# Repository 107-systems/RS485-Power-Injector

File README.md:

`RS485-Power-Injector`
======================

This repository contains the design files for [L3X-Z](https://github.com/107-systems/l3xz)'s RS485 power injector which allows to directly inject battery power into the RS485 bus connecting the robot's Dynamixel MX-28AR servos.

<p align="center">
  
</p>

## Debug circuitry

This board contains a circuit with a RS485 driver to drive a LED to show bus activity. This circuit can also be used to interface the RS485 bus to a controller or computer. The circuit can be used with 3.3V and 5V levels. Some parts need to be changed to achieve this.

| **Designator** | **3.3V version** | **5V version** |
|:--------------:|:----------------:|:--------------:|
| U1             | L78L33ACUTR      | L78L05ACUTR    |
| U2             | SP3485EN-L       | SN75176AD      |

## Connectors

### Power Input J1
Anderson Power Pole

| **Pin** | **Signal**    |       **Description**        |
|:-------:|:-------------:|:----------------------------:|
| 1       | +BATT         | Directly to Dynamixel        |
| 2       | GND           |                              |

The input voltage is directly feed to the Dynamixel servo. So the maximum voltage depends solely on the servo used.

### Power Input J2
Würth WR-TBL 3.5mm 2-pin screw terminal.

| **Pin** | **Signal**    |       **Description**        |
|:-------:|:-------------:|:----------------------------:|
| 1       | +BATT         | Directly to Dynamixel        |
| 2       | GND           |                              |

### RS485 Input J3
Würth WR-TBL 3.5mm 3-pin screw terminal.

| **Pin** | **Signal**    |       **Description**        |
|:-------:|:-------------:|:----------------------------:|
| 1       | RS485-A       | Directly to Dynamixel        |
| 2       | RS485-B       | Directly to Dynamixel        |
| 3       | GND           |                              |

### RS485 Input J4
JST GH 1.25mm 4-pin.

| **Pin** | **Signal**    |       **Description**        |
|:-------:|:-------------:|:----------------------------:|
| 1       | +BATT         | to Dynamixel via R2          |
| 2       | RS485-A       | Directly to Dynamixel        |
| 3       | RS485-B       | Directly to Dynamixel        |
| 4       | GND           |                              |

### Dynamixel connectors J5 and J6
In the Dynamixel world there exist two type of connectors: [Molex Mini-SPOX](https://www.molex.com/molex/products/part-detail/pcb_headers/0022035045) and [JST EH](https://www.jst-mfg.com/product/pdf/eng/eEH.pdf).

Both are 2.5 mm pitch and use the same pin out and both can be mounted on the board. So you can decide which one to use and which fits your application and servo.

| **Pin** | **Signal**    |       **Description**        |
|:-------:|:-------------:|:----------------------------:|
| 1       | GND           |                              |
| 2       | +BATT         |                              |
| 3       | RS485-A       |                              |
| 4       | RS485-B       |                              |

### RS485 Debug output J7
Pin header 2.54mm 4-pin.

| **Pin** | **Signal**    |       **Description**        |
|:-------:|:-------------:|:----------------------------:|
| 1       | RS485_TXEN    |                              |
| 2       | RS485_TX      |                              |
| 3       | RS485_RX      |                              |
| 4       | GND           |                              |

## Enclosure

There exists a 3D printable enclosure to encapsulate the PCB.

### Standard

## PCB
### Top

### Bottom

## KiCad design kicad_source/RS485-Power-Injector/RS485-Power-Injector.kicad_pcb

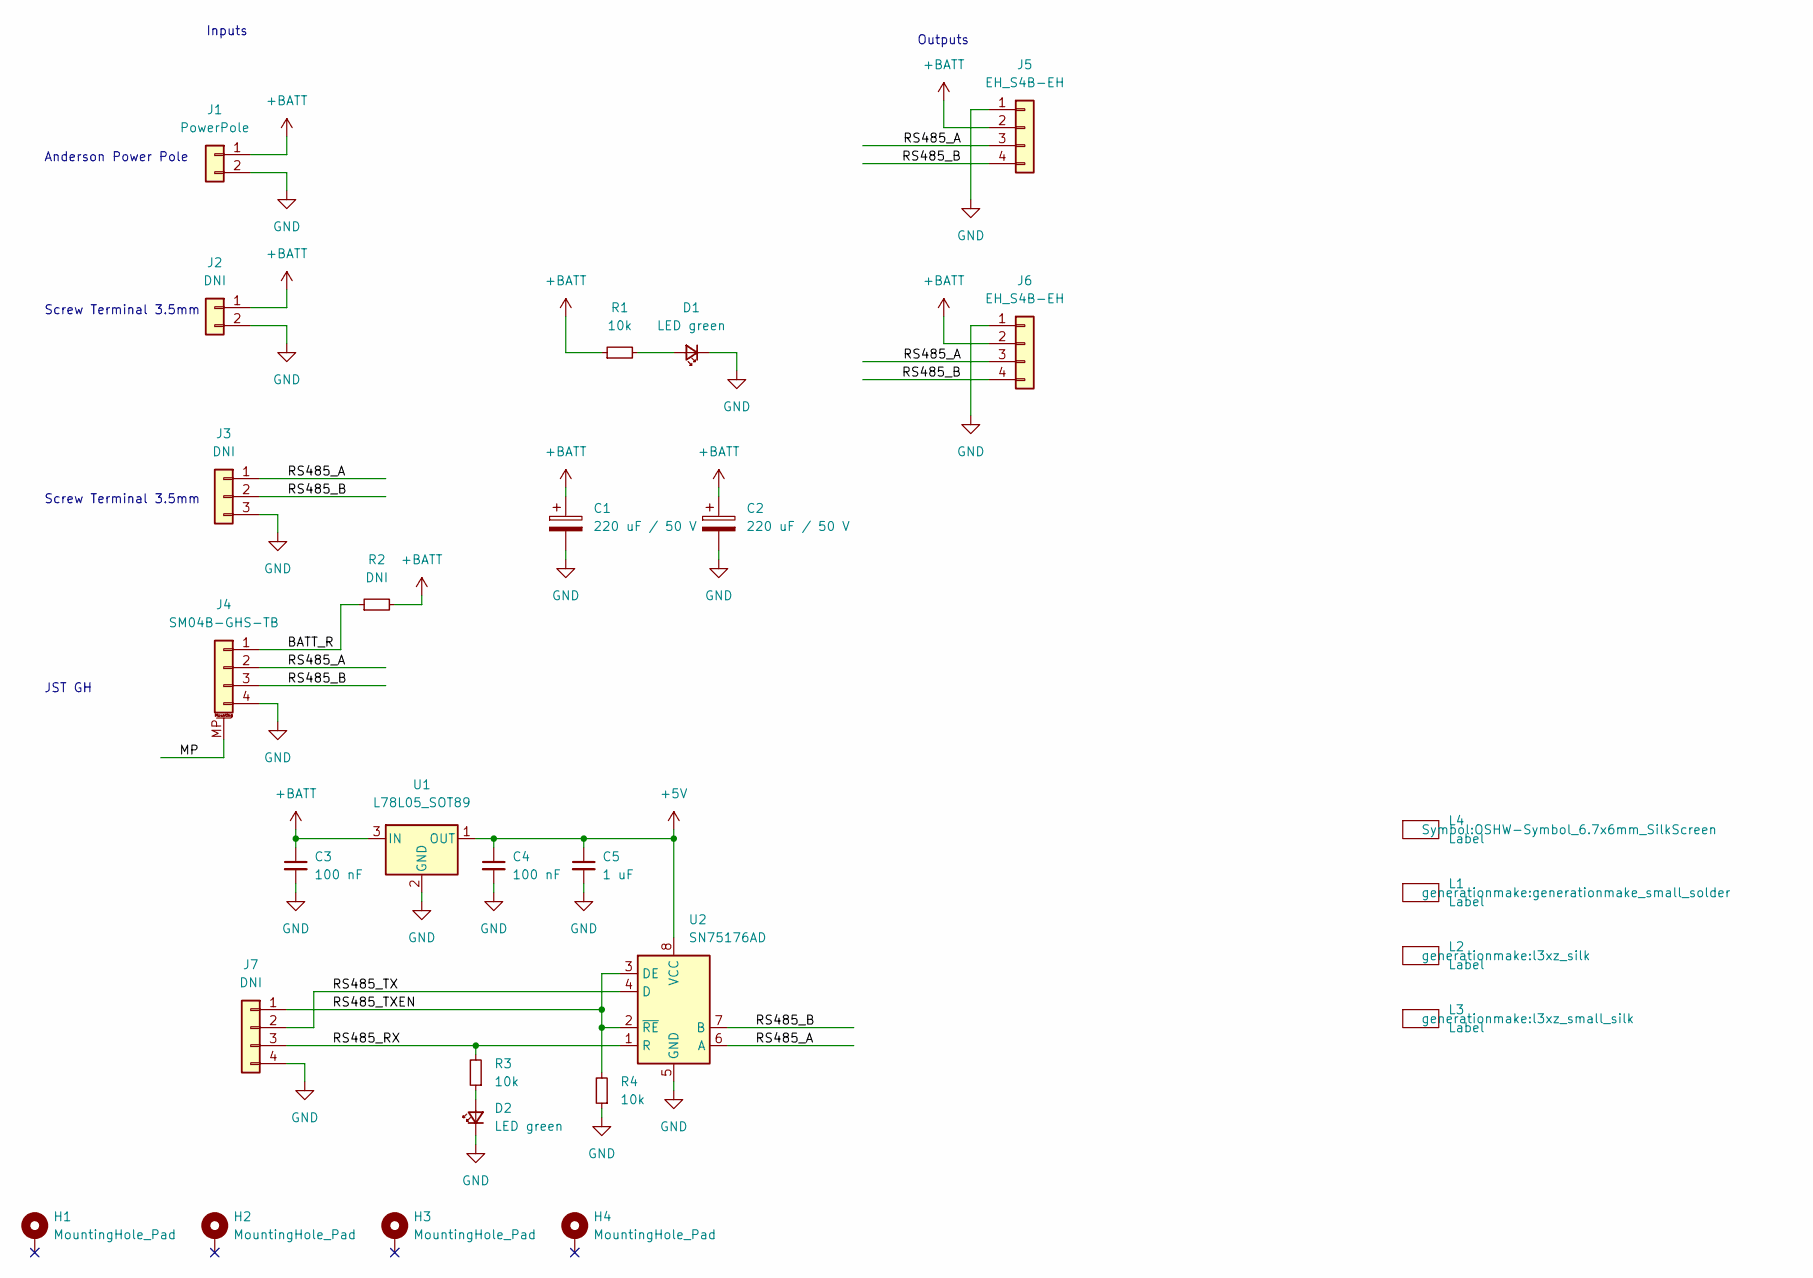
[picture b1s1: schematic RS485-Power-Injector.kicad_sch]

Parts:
C1, C2: 220 uF / 50 V; CP_Elec_10x14.3
C3, C4: 100 nF; C_0603_1608Metric
C5: 1 uF; C_0603_1608Metric
D1, D2: LED green; LED_0603_1608Metric
H1, H2, H3, H4: MountingHole_Pad; MountingHole_3.2mm_M3_DIN965_Pad
J1: PowerPole; POWERPOLE_hor_2
J2: DNI; PhoenixContact_MC_1,5_2-G-3.5_1x02_P3.50mm_Horizontal
J3: DNI; PhoenixContact_MC_1,5_3-G-3.5_1x03_P3.50mm_Horizontal
J4: SM04B-GHS-TB; JST_GH_SM04B-GHS-TB_1x04-1MP_P1.25mm_Horizontal
J5, J6: EH_S4B-EH; JST_EH_S4B-EH_1x04_P2.50mm_Horizontal
J7: DNI; PinHeader_1x04_P2.54mm_Vertical
L1: Label; generationmake_small_solder
L2: Label; l3xz_silk
L3: Label; l3xz_small_silk
L4: Label; OSHW-Symbol_6.7x6mm_SilkScreen
R1, R3, R4: 10k; R_0603_1608Metric
R2: DNI; R_0603_1608Metric
U1: L78L05_SOT89; SOT-89-3
U2: SN75176AD; SOIC-8_3.9x4.9mm_P1.27mm

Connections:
+5V: C4.1, C5.1, U1.1 (OUT), U2.8 (VCC)
+BATT: C1.1, C2.1, C3.1, J1.1, J2.1, J5.2, J6.2, R1.1, R2.2, U1.3 (IN)
/BATT_R: J4.1, R2.1
/MP: J4.MP (MountPin)
/RS485_A: J3.1, J4.2, J5.3, J6.3, U2.6 (A)
/RS485_B: J3.2, J4.3, J5.4, J6.4, U2.7 (B)
/RS485_RX: J7.3, R3.2, U2.1 (R)
/RS485_TX: J7.2, U2.4 (D)
/RS485_TXEN: J7.1, R4.2, U2.2 (~RE), U2.3 (DE)
GND: C1.2, C2.2, C3.2, C4.2, C5.2, D1.1 (K), D2.1 (K), J1.2, J2.2, J3.3, J4.4, J5.1, J6.1, J7.4, R4.1, U1.2 (GND), U2.5 (GND)
unnamed: D1.2 (A), R1.2
unnamed: D2.2 (A), R3.1

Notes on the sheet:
JST GH
Outputs
Anderson Power Pole
Screw Terminal 3.5mm
Inputs

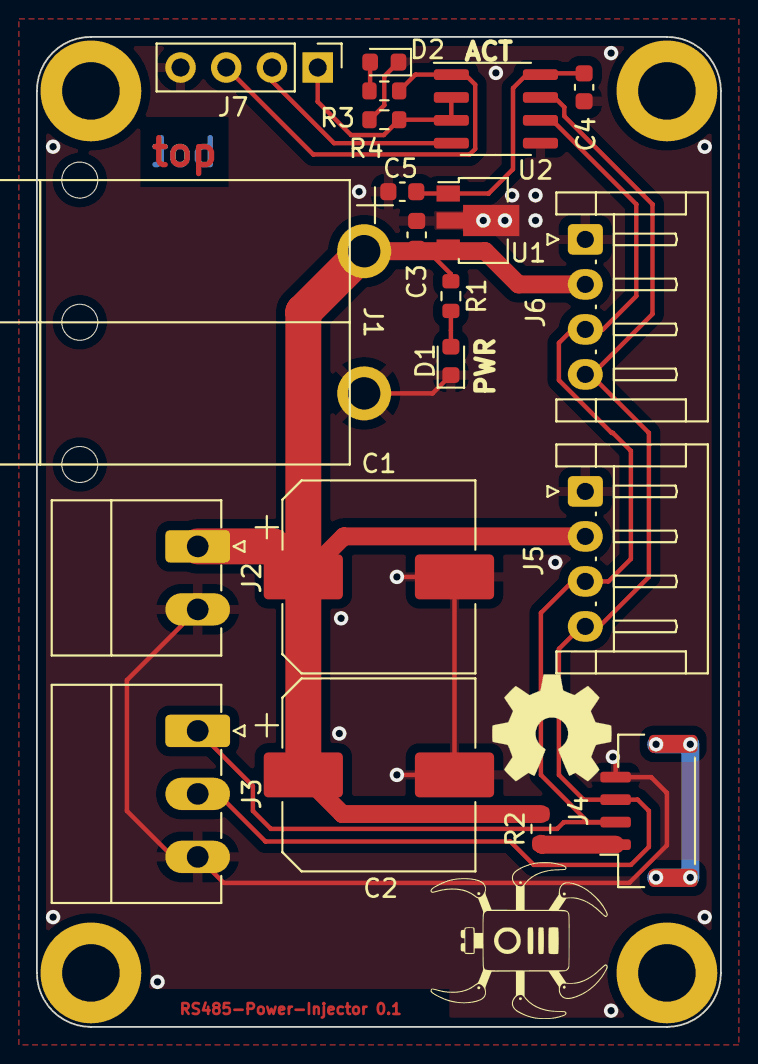
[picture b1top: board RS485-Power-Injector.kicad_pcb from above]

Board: 2 copper layers, 38.0 x 55.0 mm, 28 parts (1 on the bottom side), 11 nets.

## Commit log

2023-01-07 Initial commit.
2023-01-07 License this project unter CERN OHL v2 (permissive).
2023-01-07 Ignore LICENSE.txt for spell checking.
2023-01-07 added kicad project
2023-01-07 updated pcb
2023-01-08 added schematic pdf
2023-01-08 added images
2023-01-09 Change license to CERN-OHL-W 2.0.
2023-01-18 Change license to CERN-OHL-W 2.0. (#2)
2023-01-21 added resistor to connect JST GH connector to +BATT
2023-01-21 added RS-485 transceiver and status LED
2023-01-21 added mounting pad on JST GH connector
2023-01-21 added some labels
2023-01-21 updated schematic pdf and images
2023-01-23 generated BOM
2023-01-23 added some gnd vias
2023-02-16 Rename from l3xz-hw-rs485-power-injector to RS485-Power-Injector.
2023-02-16 Rename from l3xz-hw-rs485-power-injector to RS485-Power-Injector. (#7)
2023-02-16 Fix CI spell check action. Exclude kicad_source folder from spell checking.
2023-02-16 Fix CI spell check action. (#8)
    Exclude kicad_source folder from spell checking.
2023-02-16 updated footprints, generated step file
2023-02-16 added freecad project and first draft of enclosure
2023-02-16 updated dimensions
2023-02-16 excluded step from spellcheck
2023-02-16 added stl production data and image of enclosure
2023-04-09 updated readme with dynamixel connector info
2023-04-09 added holes for LEDs
2023-04-09 added lid over connectors, updated stl file
2023-04-09 updated image
2023-04-10 updated readme with info on 3v3 version
2023-04-10 Fix: captions should start with uppercase.
2023-04-10 Fix: captions should start with uppercase. (#16)
2023-04-10 Fix: use proper markdown links.
2023-04-10 Add missing dot.
2023-04-10 Fix: use proper markdown links. (#17)
2023-08-09 Bump carlosperate/download-file-action from 2.0.0 to 2.0.1
    Bumps [carlosperate/download-file-action](https://github.com/carlosperate/download-file-action) from 2.0.0 to 2.0.1.
    - [Release notes](https://github.com/carlosperate/download-file-action/releases)
    - [Commits](https://github.com/carlosperate/download-file-action/compare/v2.0.0...v2.0.1)
    ---
    updated-dependencies:
    - dependency-name: carlosperate/download-file-action
2023-08-09 Bump carlosperate/download-file-action from 2.0.0 to 2.0.1 (#18)
    Bumps [carlosperate/download-file-action](https://github.com/carlosperate/download-file-action) from 2.0.0 to 2.0.1.
    - [Release notes](https://github.com/carlosperate/download-file-action/releases)
    - [Commits](https://github.com/carlosperate/download-file-action/compare/v2.0.0...v2.0.1)
    ---
    updated-dependencies:
    - dependency-name: carlosperate/download-file-action
2023-09-05 Bump actions/checkout from 3 to 4
    Bumps [actions/checkout](https://github.com/actions/checkout) from 3 to 4.
    - [Release notes](https://github.com/actions/checkout/releases)
    - [Changelog](https://github.com/actions/checkout/blob/main/CHANGELOG.md)
    - [Commits](https://github.com/actions/checkout/compare/v3...v4)
    ---
    updated-dependencies:
2023-09-05 Bump actions/checkout from 3 to 4 (#19)
    Bumps [actions/checkout](https://github.com/actions/checkout) from 3 to 4.
    - [Release notes](https://github.com/actions/checkout/releases)
    - [Changelog](https://github.com/actions/checkout/blob/main/CHANGELOG.md)
    - [Commits](https://github.com/actions/checkout/compare/v3...v4)
    ---
    updated-dependencies:
2023-12-15 Bump actions/download-artifact from 3 to 4
    Bumps [actions/download-artifact](https://github.com/actions/download-artifact) from 3 to 4.
    - [Release notes](https://github.com/actions/download-artifact/releases)
    - [Commits](https://github.com/actions/download-artifact/compare/v3...v4)
    ---
    updated-dependencies:
    - dependency-name: actions/download-artifact
2023-12-15 Bump actions/upload-artifact from 3 to 4
    Bumps [actions/upload-artifact](https://github.com/actions/upload-artifact) from 3 to 4.
    - [Release notes](https://github.com/actions/upload-artifact/releases)
    - [Commits](https://github.com/actions/upload-artifact/compare/v3...v4)
    ---
    updated-dependencies:
    - dependency-name: actions/upload-artifact
2023-12-15 Bump actions/upload-artifact from 3 to 4 (#21)
    Bumps [actions/upload-artifact](https://github.com/actions/upload-artifact) from 3 to 4.
    - [Release notes](https://github.com/actions/upload-artifact/releases)
    - [Commits](https://github.com/actions/upload-artifact/compare/v3...v4)
    ---
    updated-dependencies:
    - dependency-name: actions/upload-artifact
2023-12-15 Bump actions/download-artifact from 3 to 4 (#20)
    Bumps [actions/download-artifact](https://github.com/actions/download-artifact) from 3 to 4.
    - [Release notes](https://github.com/actions/download-artifact/releases)
    - [Commits](https://github.com/actions/download-artifact/compare/v3...v4)
    ---
    updated-dependencies:
    - dependency-name: actions/download-artifact
2023-12-25 Bump geekyeggo/delete-artifact from 2 to 4
    Bumps [geekyeggo/delete-artifact](https://github.com/geekyeggo/delete-artifact) from 2 to 4.
    - [Release notes](https://github.com/geekyeggo/delete-artifact/releases)
    - [Changelog](https://github.com/GeekyEggo/delete-artifact/blob/main/CHANGELOG.md)
    - [Commits](https://github.com/geekyeggo/delete-artifact/compare/v2...v4)
    ---
    updated-dependencies:
2023-12-25 Bump geekyeggo/delete-artifact from 2 to 4 (#22)
    Bumps [geekyeggo/delete-artifact](https://github.com/geekyeggo/delete-artifact) from 2 to 4.
    - [Release notes](https://github.com/geekyeggo/delete-artifact/releases)
    - [Changelog](https://github.com/GeekyEggo/delete-artifact/blob/main/CHANGELOG.md)
    - [Commits](https://github.com/geekyeggo/delete-artifact/compare/v2...v4)
    ---
    updated-dependencies:
2024-03-19 Bump geekyeggo/delete-artifact from 4 to 5
    Bumps [geekyeggo/delete-artifact](https://github.com/geekyeggo/delete-artifact) from 4 to 5.
    - [Release notes](https://github.com/geekyeggo/delete-artifact/releases)
    - [Changelog](https://github.com/GeekyEggo/delete-artifact/blob/main/CHANGELOG.md)
    - [Commits](https://github.com/geekyeggo/delete-artifact/compare/v4...v5)
    ---
    updated-dependencies:
2024-03-19 Bump geekyeggo/delete-artifact from 4 to 5 (#23)
    Bumps [geekyeggo/delete-artifact](https://github.com/geekyeggo/delete-artifact) from 4 to 5.
    - [Release notes](https://github.com/geekyeggo/delete-artifact/releases)
    - [Changelog](https://github.com/GeekyEggo/delete-artifact/blob/main/CHANGELOG.md)
    - [Commits](https://github.com/geekyeggo/delete-artifact/compare/v4...v5)
    ---
    updated-dependencies:
